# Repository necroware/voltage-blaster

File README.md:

# Voltage Blaster

Voltage Blaster is a very simple circuit, which provides -5V through ISA slot
for systems with power supply which don't provide such voltage. It was created
in cooperation of PhilsComputerLab with Necroware.

## Why do I need this?

Back in the days of XT and AT compatible computers the standard power supply had
to provide 5V, 12V, -12V and -5V. A lot of hardware, especially sound cards,
needed -5V to work properly. This voltage was provided for the ISA expansion
cards on the pin B5. As time passed, AT systems and compatible power supplies
were replaced by ATX. In the beginning they also provided -5V, but then less and
less expansion cards needed such voltage and as soon as ISA was considered 
obsolete, ATX standard eventually dropped -5V rail requirement. Today it is not
possible to buy a new AT power supply, but ATX power supplies can be used
through an adapter. However, since almost none of the modern ATX power supplies
will provide -5V, you could run into problems, when trying to use an old ISA
expansion card, which needs this voltage. Famous examples are Creative Sound
Blaster 2.0, Pro Audio Spectrum sound cards and many others. This is where the
Voltage Blaster comes into play.

## How does it work?

All voltage pins in the ISA slots are directly connected to each other and to
the PSU. When using a PSU without -5V support, the ISA slot pin B5 is just
floating. The idea behind the Voltage Blaster is very simple. What if one of the
ISA expansion cards will provide -5V and feed it through the ISA slot in
reverse. Well since the ISA slot pin B7 provides -12V, it's just a matter of
using a linear voltage regulator LM7905 and connect its output to the pin B5 of
the ISA slot.

## Bill of materials

Reference  |#  |LCSC   |Description
-----------|---|-------|-------------------------------------
U1         | 1 |C427634| linear voltage regulator LM7905
C1,C2      | 2 |C3314  | electrolytic capacitor 33µF
D1         | 1 |C99697 | light emitting diode (optional)
R1         | 1 |C58608 | resistor 330 Ohm (optional)

Parts D1 and R1 are optional and are only required if you want that the diode is
lighting, when -5V are generated.

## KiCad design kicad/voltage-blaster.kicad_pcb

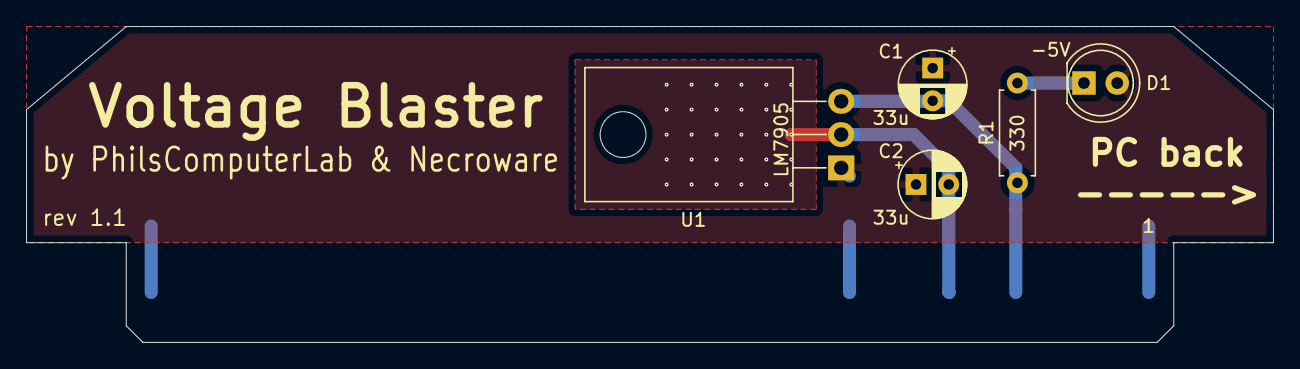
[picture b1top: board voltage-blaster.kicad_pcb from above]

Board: 2 copper layers, 95.2 x 24.1 mm, 6 parts (0 on the bottom side), 4 nets.

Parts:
C1, C2: 33u; CP_Radial_D5.0mm_P2.50mm
D1: -5V; LED_D5.0mm
J1: Bus_ISA_8bit; ISA_8BIT_EDGE
R1: 330; R_Axial_DIN0207_L6.3mm_D2.5mm_P7.62mm_Horizontal
U1: LM7905; TO-220-3_Horizontal_TabDown

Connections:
GND: C1.1, C2.1, D1.2, J1.1, J1.10, J1.31, U1.1
unnamed: C1.2, J1.5, R1.1, U1.3
unnamed: C2.2, J1.7, U1.2
unnamed: D1.1, R1.2

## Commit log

2020-11-23 Regenerated gerber files
2020-12-08 Remove gerber files from the project
2020-12-08 Add some markings on the back side.
    This is actually not necessary, but having this markings there will
    enforce JLCPCB to print their serial number on the back side as well
2020-12-08 Add some documentation
2020-12-08 Add BOM to readme
2020-12-08 Add LCSC parts numbers to the schema
2020-12-08 Readme cleanup
2021-02-23 Remove License
2021-02-24 Switch to CC0 License
2021-05-23 Improved PCB layout
    - removed solder mask on LM7905 cooling area
    - increased cooling area on the back side
    - added micro vias for better thermal transport
    - removed unused socket pins
2021-05-23 Remove X2 option from gerber settings
2021-05-23 Set PCB revision to 1.1
